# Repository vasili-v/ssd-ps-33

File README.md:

# Schematics for Synchronous Step-Down DC-DC Power Supply

## About

The repository contains a schematic for the Synchronous Step-Down DC-DC Power Supply with 3.6-16V input and 3.3V, 3A max output designed to operate from 4 to 8 AA or AAA batteries.

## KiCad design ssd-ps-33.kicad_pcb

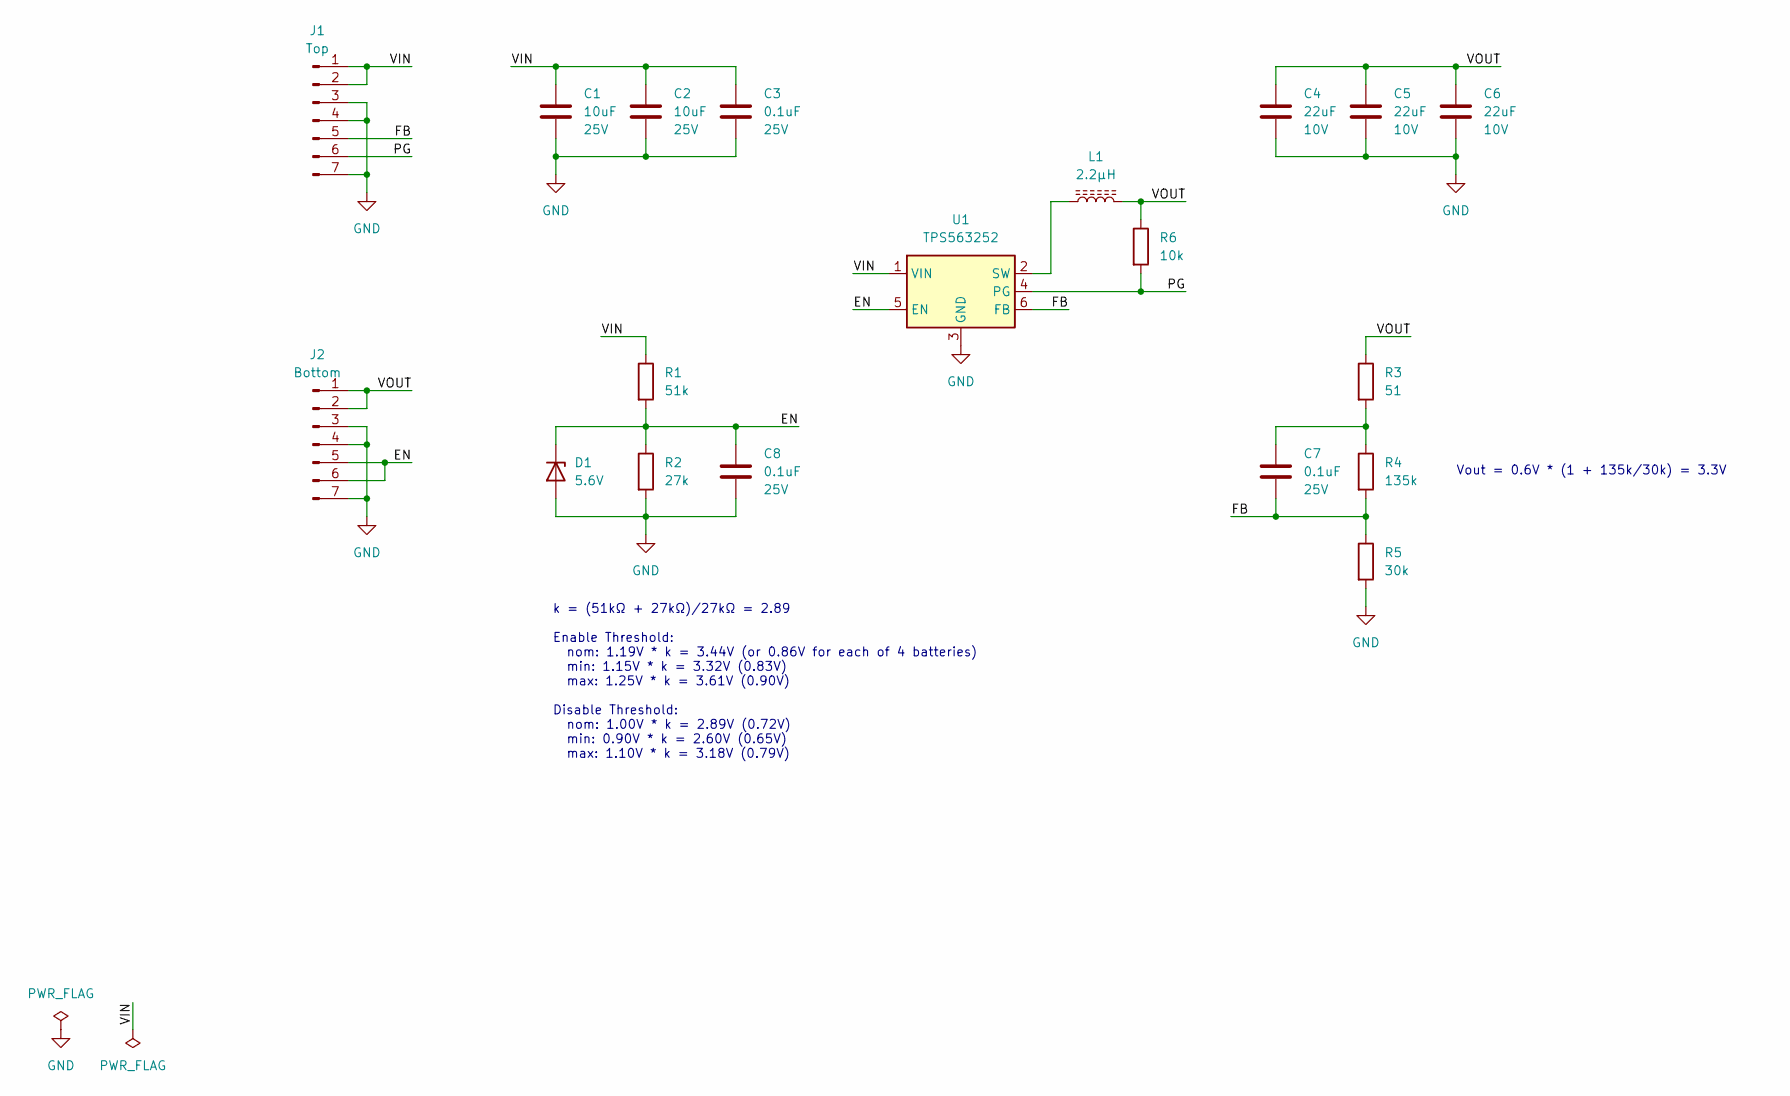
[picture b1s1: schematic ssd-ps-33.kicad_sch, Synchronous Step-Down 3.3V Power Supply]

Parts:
C1, C2: 10uF; C_0805_2012Metric; Rated Voltage 25V; Part Number GRM21BR61E106MA73L
C3, C7, C8: 0.1uF; C_0603_1608Metric_Pad1.08x0.95mm_HandSolder; Rated Voltage 25V; Part Number CC0603KRX7R8BB104
C4, C5, C6: 22uF; C_0805_2012Metric; Rated Voltage 10V; Part Number GRM21BR61A226ME44L
D1: 5.6V; D_SOD-323_HandSoldering
J1: Top; PinHeader_1x07_P2.54mm_Vertical_No_Silkscreen
J2: Bottom; PinHeader_1x07_P2.54mm_Vertical_No_Silkscreen
L1: 2.2µH; L_Chilisin_BWVS00505040; Part Number BWVS005050402R2M00
R1: 51k; R_0603_1608Metric_Pad0.98x0.95mm_HandSolder
R2: 27k; R_0603_1608Metric_Pad0.98x0.95mm_HandSolder
R3: 51; R_0603_1608Metric_Pad0.98x0.95mm_HandSolder
R4: 135k; R_0603_1608Metric_Pad0.98x0.95mm_HandSolder
R5: 30k; R_0603_1608Metric_Pad0.98x0.95mm_HandSolder
R6: 10k; R_0603_1608Metric_Pad0.98x0.95mm_HandSolder
U1: TPS563252; SOT-563; Part Number TPS563252DRLR

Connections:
/EN: C8.1, D1.1 (K), J2.5, J2.6, R1.2, R2.1, U1.5 (EN)
/FB: C7.2, J1.5, R4.2, R5.1, U1.6 (FB)
/PG: J1.6, R6.2, U1.4 (PG)
/VIN: C1.1, C2.1, C3.1, J1.1, J1.2, R1.1, U1.1 (VIN)
/VOUT: C4.1, C5.1, C6.1, J2.1, J2.2, L1.2, R3.1, R6.1
GND: C1.2, C2.2, C3.2, C4.2, C5.2, C6.2, C8.2, D1.2 (A), J1.3, J1.4, J1.7, J2.3, J2.4, J2.7, R2.2, R5.2, U1.3 (GND)
unnamed: C7.1, R3.2, R4.1
unnamed: L1.1, U1.2 (SW)

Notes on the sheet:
Vout = 0.6V * (1 + 135k/30k) = 3.3V
k = (51kΩ + 27kΩ)/27kΩ = 2.89 Enable Threshold: nom: 1.19V * k = 3.44V (or 0.86V for each of 4 batteries) min: 1.15V * k = 3.32V (0.83V) max: 1.25V * k = 3.61V (0.90V) Disable Threshold: nom: 1.00V * k = 2.89V (0.72V) min: 0.90V * k = 2.60V (0.65V) max: 1.10V * k = 3.18V (0.79V)

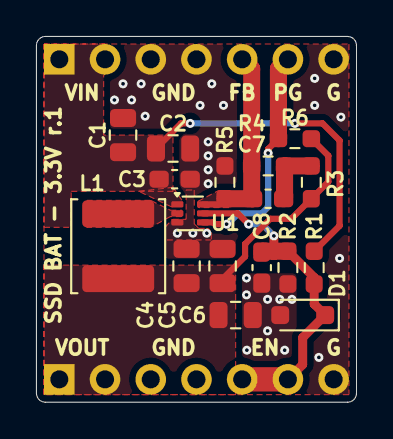
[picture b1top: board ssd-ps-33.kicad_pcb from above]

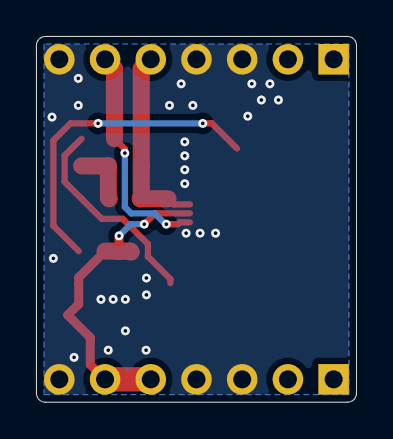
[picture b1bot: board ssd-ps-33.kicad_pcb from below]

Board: 2 copper layers, 17.8 x 20.3 mm, 19 parts (2 on the bottom side), 8 nets.

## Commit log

2026-04-08 Create starter support files for the project
2026-04-14 Add initial KiCad project files
2026-04-15 Add symbol for converter
2026-04-15 Put controller and filter capacitors to schematic
2026-04-16 Create main schematics without connectors for now
2026-04-16 Preliminary place components
2026-04-24 Draft routing, board size and select connectors
2026-04-24 Set values for enable network and fix DRC errors
2026-04-24 Place part's references
2026-04-26 Add designators to pins and board name
2026-04-26 Change board name and add revision
2026-04-27 Add FB to top connector and finalize routing
2026-04-27 Round PCB corners
2026-04-27 Setup fabrication output
2026-04-28 Complete BOM with market available parts
